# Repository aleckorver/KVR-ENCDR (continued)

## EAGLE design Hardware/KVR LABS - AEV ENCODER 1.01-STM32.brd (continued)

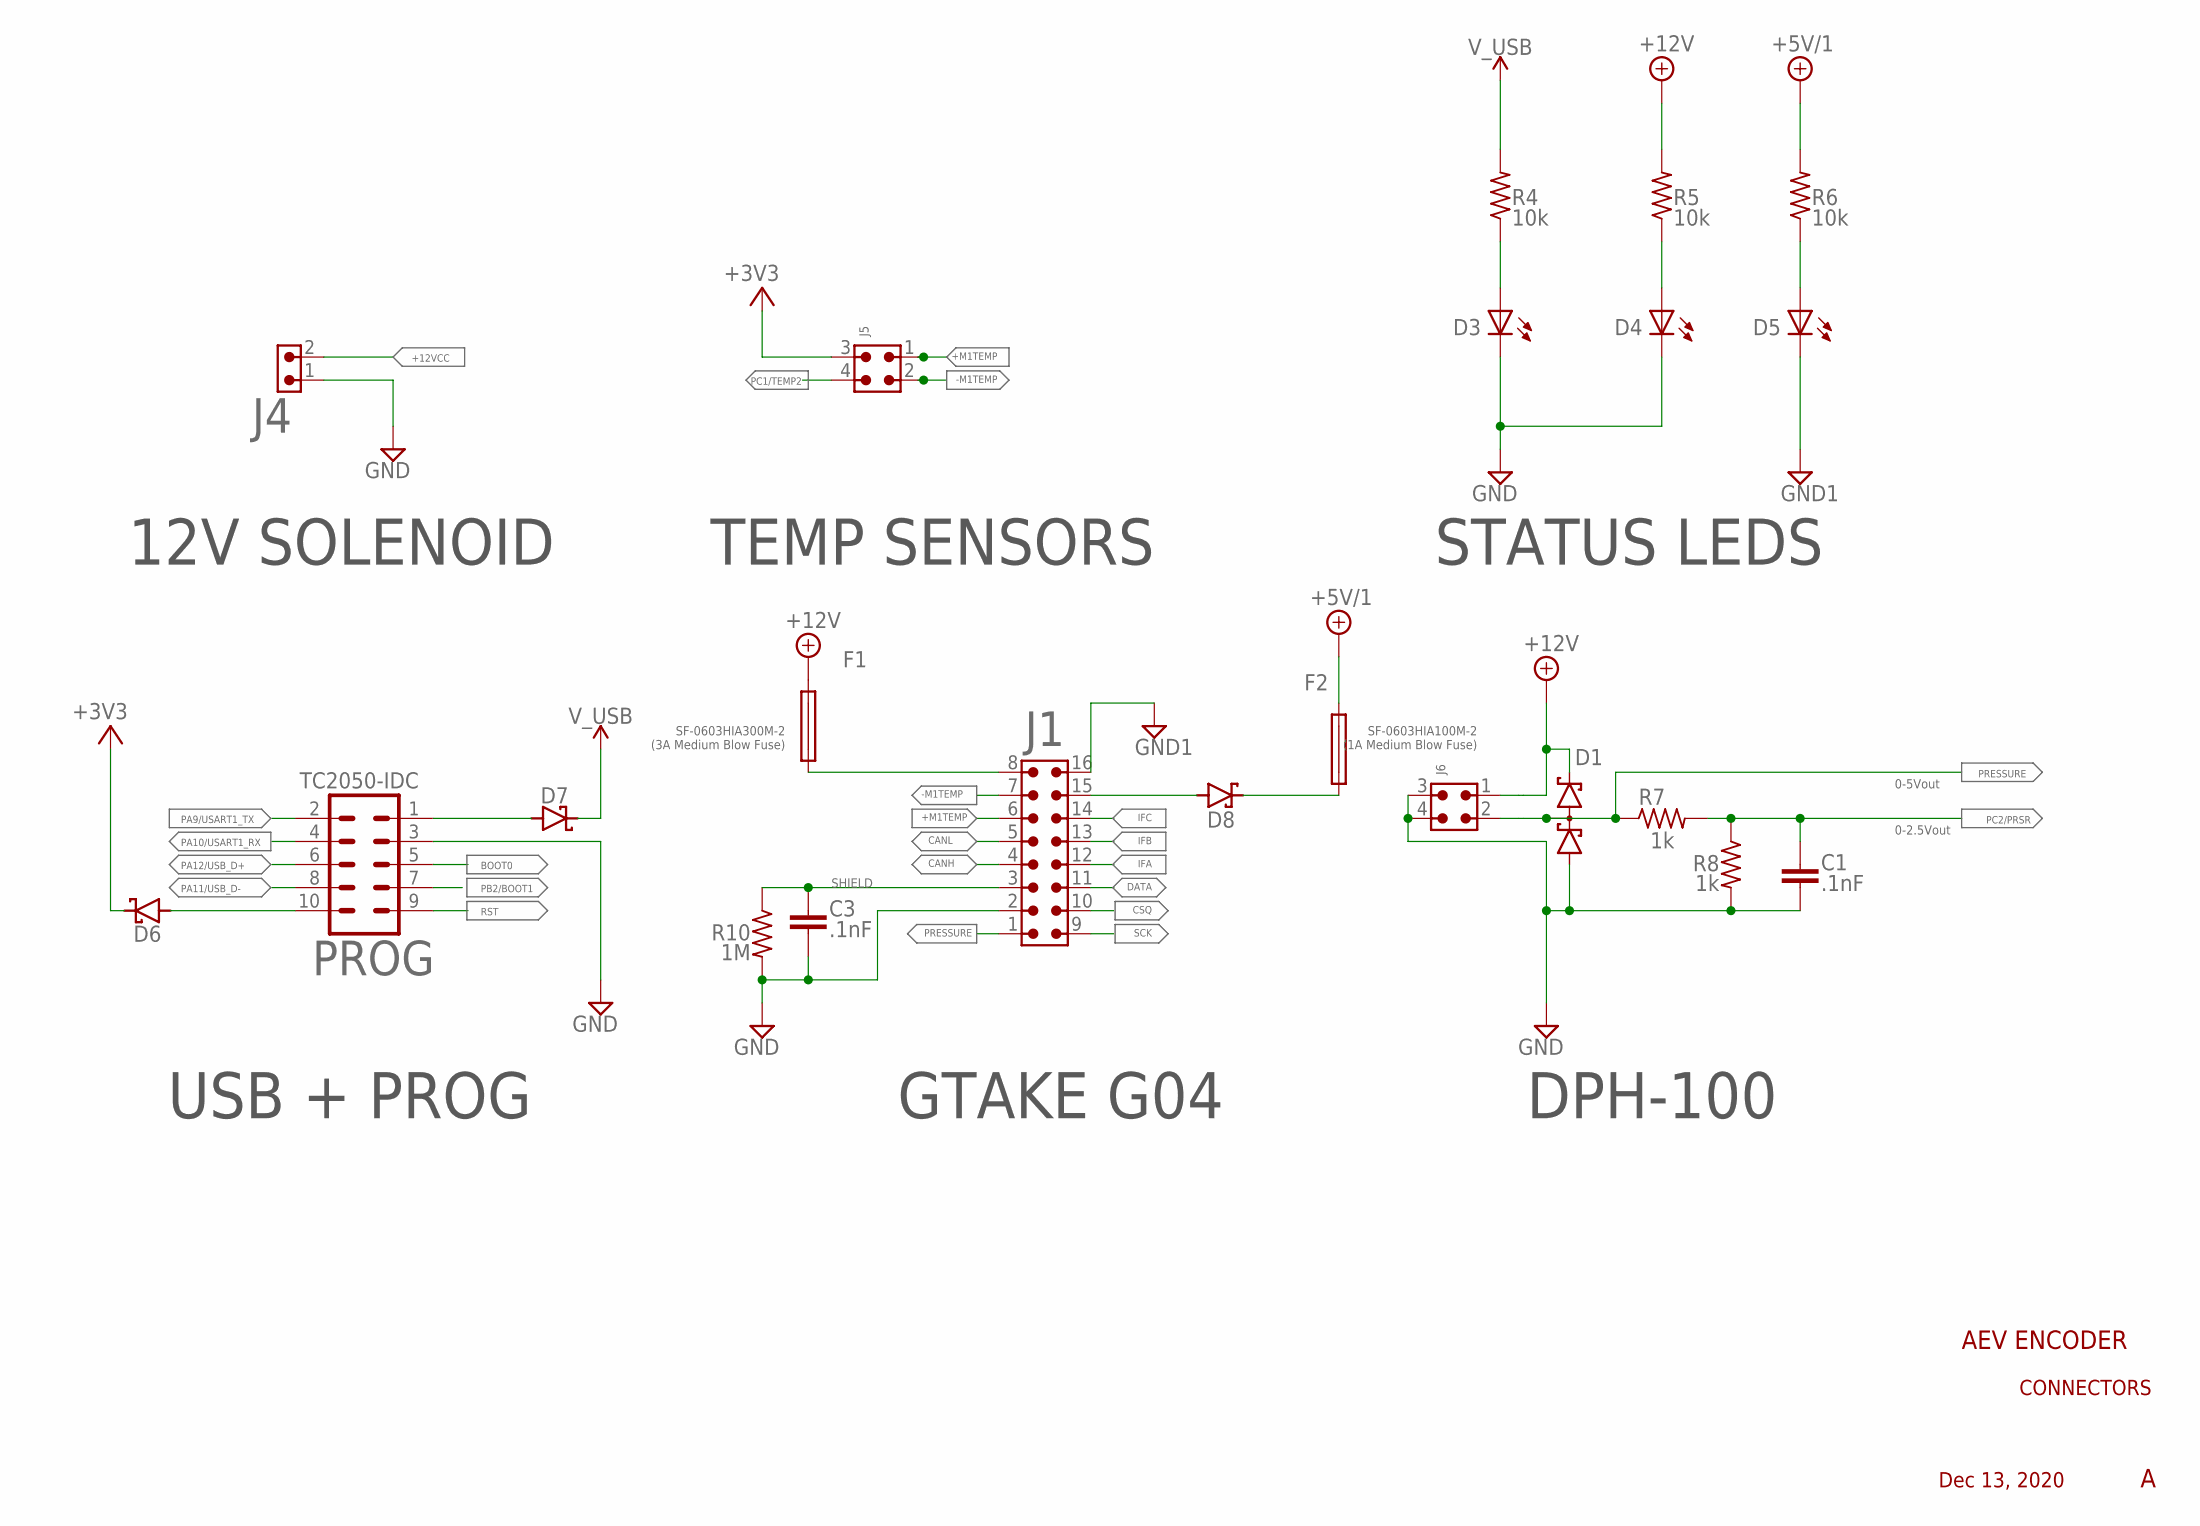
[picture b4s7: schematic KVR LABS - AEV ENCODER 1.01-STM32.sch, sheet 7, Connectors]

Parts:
C1, C3: .1nF; C0603
D1: BAS70-04; SOT23
D3, D4, D5: LEDCHIPLED_0805; CHIPLED_0805
D6, D7, D8: MBR0520LT1G; SODFL3718X115
F1, F2: FUSE_CHIP-0603(1608-METRIC); FUSC1608X60N
J1: 6620XX21122_66201621122; 66201621122
J4: 6620XX11122_66200211122; 66200211122
J5, J6: 6620XX21122_66200421122; 66200421122
PROG: TC2050-IDC
R4, R5, R6: 10k; R0603
R7, R8: 1k; R0603
R10: 1M; R0603

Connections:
+3V3: D6.1 (C), J5.3; also elsewhere on the board
+5V/1: F2.2, R6.2; also elsewhere on the board
+12V: D1.2 (C2), F1.2, J6.1, R5.2; also elsewhere on the board
+12VCC: J4.2; also elsewhere on the board
+M1TEMP: J1.6, J5.1
-M1TEMP: J1.7, J5.2
BOOT0: PROG.5; also elsewhere on the board
CANH: J1.4; also elsewhere on the board
CANL: J1.5; also elsewhere on the board
CSQ: J1.10; also elsewhere on the board
DATA: J1.11; also elsewhere on the board
GND: C1.2, C3.2, D1.1 (A1), D3.C, D4.C, J1.2, J4.1, J6.3, J6.4, PROG.3, R8.2, R10.2; also elsewhere on the board
GND1: D5.C, J1.16; also elsewhere on the board
IFA: J1.12; also elsewhere on the board
IFB: J1.13; also elsewhere on the board
IFC: J1.14; also elsewhere on the board
unnamed: F1.1, J1.8
unnamed: D8.1 (C), F2.1
unnamed: D6.2 (A), PROG.10
unnamed: D3.A, R4.1
unnamed: D4.A, R5.1
unnamed: D5.A, R6.1
PA9/USART1_TX: PROG.2; also elsewhere on the board
PA10/USART1_RX: PROG.4; also elsewhere on the board
PA11/USB_D-: PROG.8; also elsewhere on the board
PA12/USB_D+: PROG.6; also elsewhere on the board
PB2/BOOT1: PROG.7; also elsewhere on the board
PC1/TEMP2: J5.4; also elsewhere on the board
PC2/PRSR: C1.1, R7.2, R8.1; also elsewhere on the board
PRESSURE: D1.3 (C1A2), J1.1, J6.2, R7.1
RST: PROG.9
SCK: J1.9; also elsewhere on the board
SHIELD: C3.1, J1.3, R10.1
V_USB: D7.1 (C), R4.2; also elsewhere on the board
_+5V_ENC: D8.2 (A), J1.15
_+VBUS: D7.2 (A), PROG.1

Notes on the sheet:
USB + PROG
0-5Vout
AEV ENCODER
Dec 13, 2020
GTAKE G04
DPH-100
TEMP SENSORS
12V SOLENOID
0-2.5Vout
STATUS LEDS
CONNECTORS
SF-0603HIA300M-2 (3A Medium Blow Fuse)
SF-0603HIA100M-2 (1A Medium Blow Fuse)

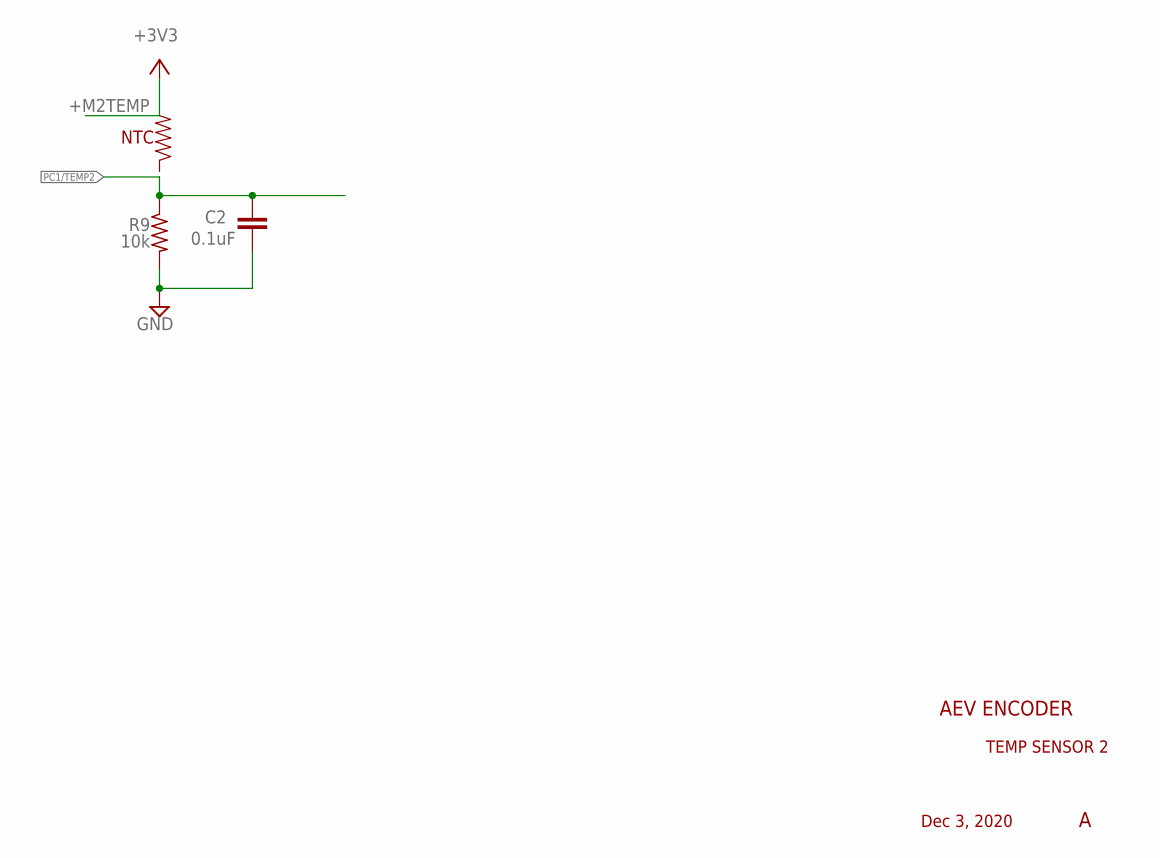
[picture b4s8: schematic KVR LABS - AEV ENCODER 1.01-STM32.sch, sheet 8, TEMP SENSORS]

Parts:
C2: 0.1uF; C0805
R9: 10k; R0603

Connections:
GND: C2.2, R9.2; also elsewhere on the board
PC1/TEMP2: C2.1, R9.1; also elsewhere on the board

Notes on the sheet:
NTC
+M2TEMP
AEV ENCODER
TEMP SENSOR 2
Dec 3, 2020

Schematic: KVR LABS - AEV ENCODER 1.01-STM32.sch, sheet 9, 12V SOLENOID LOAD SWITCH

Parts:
D2: LEDCHIPLED_0805; CHIPLED_0805
QN1: FDV305N; SOT323-3_NFET
QP1: ZXM61P02FTA; SOT323-3_NFET
R1, R2, R3: 10k; R0603

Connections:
+12V: QP1.S, R2.2; also elsewhere on the board
+12VCC: QP1.D, R3.2; also elsewhere on the board
GND: D2.C, QN1.S, R1.1; also elsewhere on the board
unnamed: QN1.D, QP1.G, R2.1
unnamed: D2.A, R3.1
PC5/SOLENOID_EN: QN1.G, R1.2; also elsewhere on the board

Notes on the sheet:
NFET FDV305N
PFET ZXM61P02FTA
Voltage Max: 20V Current Cont: 900mA Current Pulse: 2A Max
AEV ENCODER
SOLENOID SWITCH
DEC 3, 2020

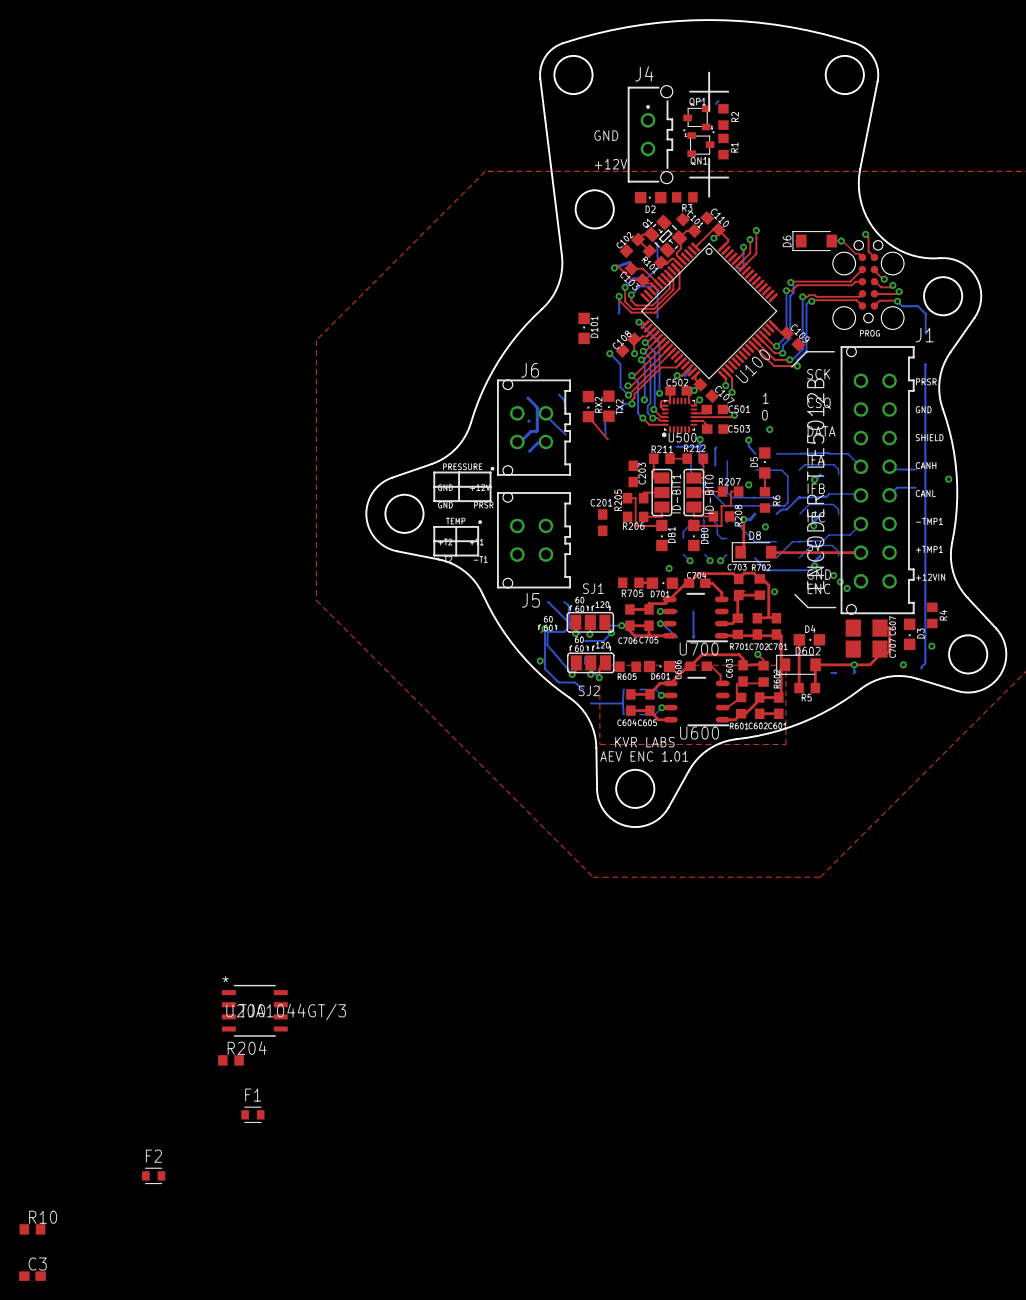
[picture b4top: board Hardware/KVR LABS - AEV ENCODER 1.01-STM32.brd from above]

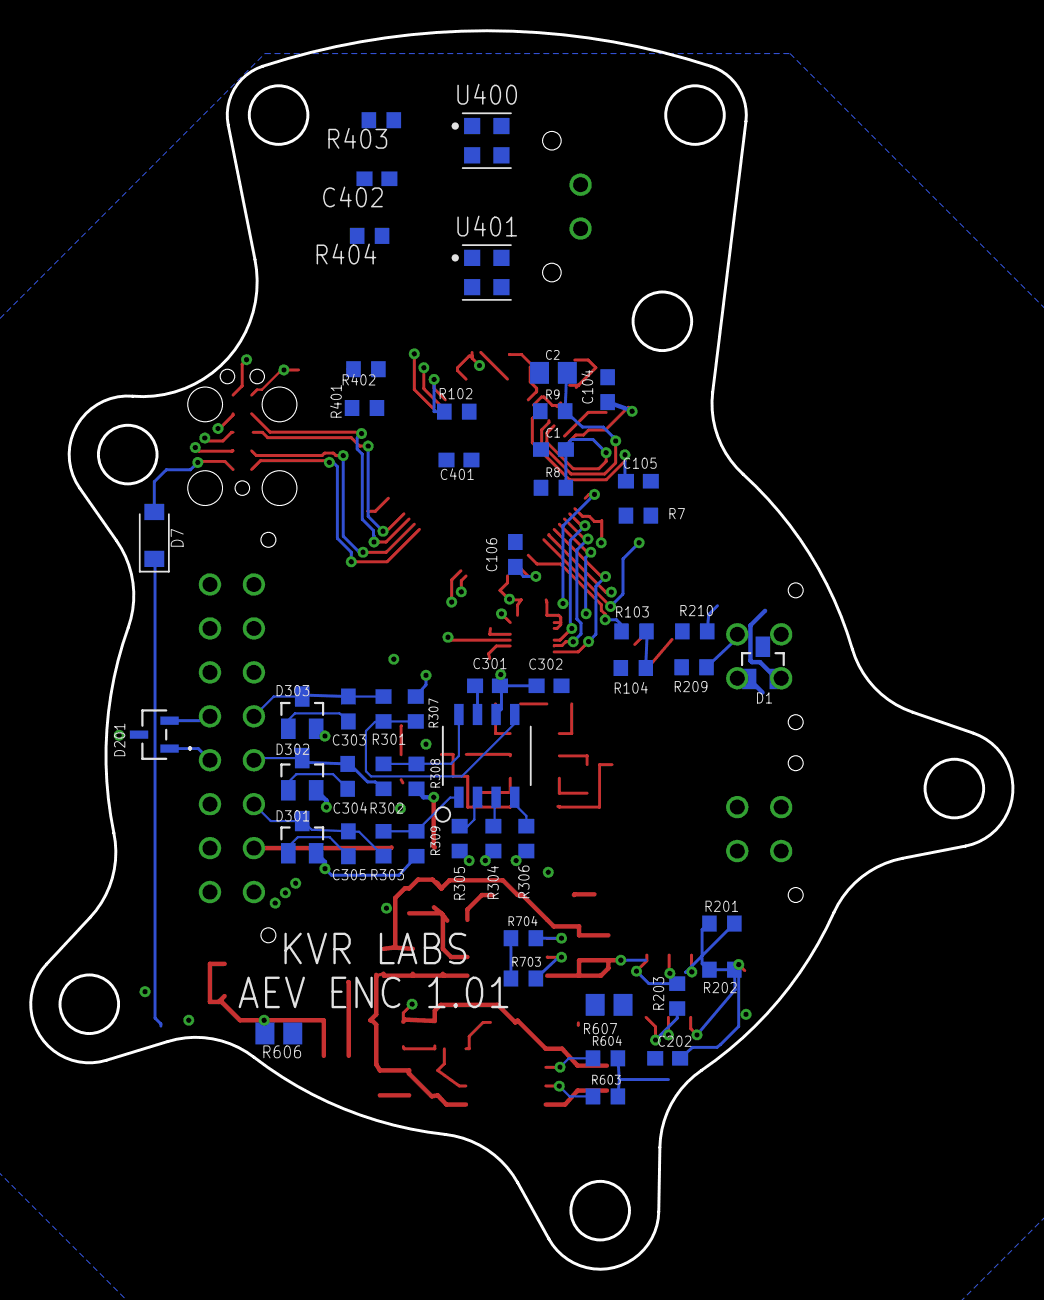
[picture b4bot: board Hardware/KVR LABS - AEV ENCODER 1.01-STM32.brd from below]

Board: 4 copper layers, 67.1 x 84.6 mm, 133 parts (52 on the bottom side), 89 nets.

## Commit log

2020-05-03 Initial Commit
    Initial Commit of hardware and firmware (IN ACTIVE DEVELOPMENT)
2020-12-15 Updated STM32
2020-12-15 Restructure
2020-12-15 Updated TVS protection
2020-12-28 Updated Schematic and layout
